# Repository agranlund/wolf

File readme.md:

## Wolfenstein 3D for Gameboy Color
 (c)2017 Anders Granlund, www.happydaze.se

A custom Gameboy Color cartridge: ATF1502 CPLD mapper, Kinetis KE04 (Cortex-M0+) as coprocessor working in tandem with Z80 on Gameboy. Commandlist and framebuffer sharing through dualport ram.

### Youtube: https://www.youtube.com/watch?v=3j6W-UF_7X0

## A rough description of what is included:

## /z80/
- ASM sourcecode for the Gameboy side, compile with WLA-DX (http://www.villehelin.com/wla.htm)
- Burn using a Gameboy flash cart programmer that support programming an AM29F040 chip via the AudioIn pin.
- I use the open-source C3 programmer from Jeff Frohwein
(https://reinerziegler.de.mirrors.gg8.se/readplus.htm#C3)
I'm sure there are more modern options out there but this is what have had since back when those things were the latest and greatest :)
Alternatively, burn the chip with a generic eprom programmer before soldering to board

## /z80/tools/
- mod2gbt, part of GBP Player 3.0.5. Built for Mac OSX.
- wla-gb, part of WLA-DX. Built for Mac OSX
- wlalink, part of WLA-DX. Built for Mac OSX

## /ke04/
- C sourcecode for MKE04Z128VLD4
- Build data using wolfgfx (makefile inside /ke04/test2/Data)
- Compile source+data with Kinetis Design Studio
- Burn with Segger J-link cable connected to SWI pins on cartridge

## /tools/wolfgfx/
- C++ source code for the map & graphics converter, with XCode project.

## /hardware/mbc/
- MBC1 clone for ATF1502AS(L)
- Compile with Atmel WinCUPL
- Burn with Atmel ATDH1150SUB cable connected to JTAG pins on cartridge

## /hardware/cart/
- Eagle & Gerber files for cartridge boards
- Rev.C use Nintendo MBC1 chip
- Rev.D use ATF1502 to clone MBC1 functionality
- Both are otherwise functionally identical
- Manufacture the board in 0.8mm height

## /hardware/link/
- Eagle & Gerber files for cartridge <-> JTAG & SWI cables
- Optional adapter to make connecting programming cables more convenient

## External libraries and credits

### Wolf4SDL:
Portions of this software derivate from Wolf4SDL by Moritz "Ripper" Kroll
(http://www.chaos-software.de.vu)

Wolf4SDL is in turned based on Wolfenstein 3D by id Software.
(http://www.idsoftware.com)

### FX HAMMER:
This software is using FX Hammer by Aleksi Eeben for generating and playing
sound effects. https://aleksieeben.myportfolio.com/portfolio

### GBT PLAYER:
This software is using GBT PLAYER v3.0.5 for music playback and for converting the
midis to runtime format. https://github.com/AntonioND/gbt-player

The converter tool in z80/tools/mod2gbt was built for MacOSX. Please see
the official GBT-Player Github page if you need to build it for another
operating system.

## License

 This hardware and software is free; you can redistribute it and/or
 modify it under the terms of the GNU General Public License
 as published by the Free Software Foundation; either version 2
 of the License, or (at your option) any later version.

 It is being distributed in the hope that it will be useful,
 but WITHOUT ANY WARRANTY; without even the implied warranty of
 MERCHANTABILITY or FITNESS FOR A PARTICULAR PURPOSE.  See the
 GNU General Public License for more details.

 The Z80 binary is using FX-Hammer and GBP Player. The authors of
 these must be credited and any of their respective copyright 
 notices and/or disclaimers must be included.

 The KE04 binary uses and/or takes inspiration from parts of
 Wolf4SDL source code by Moritz "Ripper" Kroll (http://www.chaos-software.de.vu)
 which was in turn based on Wolfenstein 3D sources released by id Software.

 Some data files are derivate from the Wolfenstein 3D shareware package.

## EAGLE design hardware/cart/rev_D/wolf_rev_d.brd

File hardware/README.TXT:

------------------------------------------------------------------------------
Wolf cartridge for Gameboy Color
(c)2017 Anders Granlund, www.happydaze.se

 This hardware is free; you can redistribute it and/or
 modify it under the terms of the GNU General Public License
 as published by the Free Software Foundation; either version 2
 of the License, or (at your option) any later version.

 It is being distributed in the hope that it will be useful,
 but WITHOUT ANY WARRANTY; without even the implied warranty of
 MERCHANTABILITY or FITNESS FOR A PARTICULAR PURPOSE.  See the
 GNU General Public License for more details.
------------------------------------------------------------------------------

Feel free to use this hardware as you see fit and in accordance to the
license agreement as long as I am being credited.

Notes:
The CY7C144E appears to have been discontinued.
IDT makes a drop in replacement called 7005L15PFG but I have
not personally tested with one.

These dual-port SRAMs are rather expensive and a better solution
might be to cost reduce by using FIFOs or normal SRAM with
some added logic.

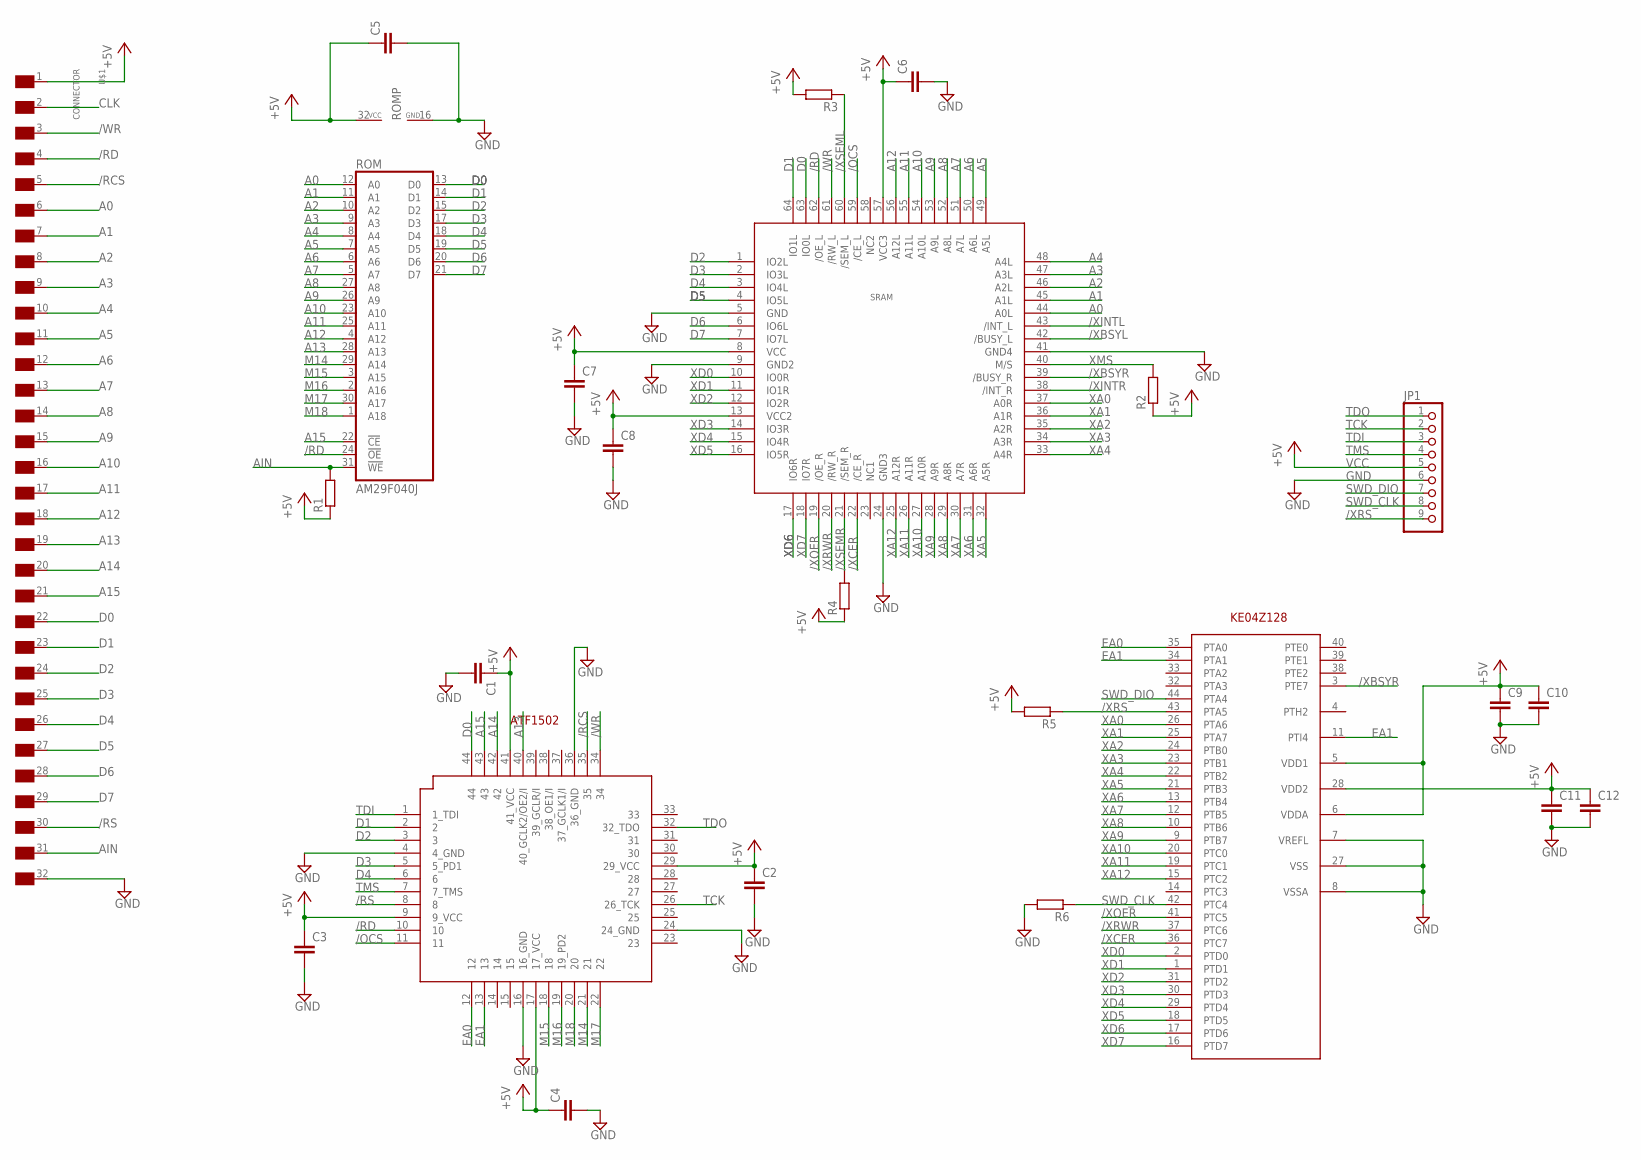
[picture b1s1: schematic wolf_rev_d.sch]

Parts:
ATF1502: ATF1502; TQFP44
C1, C2, C3, C4, C5, C6, C7, C8, C9, C10, C11, C12: C-EUC0805; C0805
JP1: PINHD-1X9; 1X09
KE04Z128: KE04Z128; TQFP44
R1, R2, R3, R4, R5, R6: R-EU_R0805; R0805
ROM: AM29F040J; PLCC32R
SRAM: CY7C144E; TQFP64
U$1: CONNECTOR

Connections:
+5V: ATF1502.9 (9_VCC), ATF1502.17 (17_VCC), ATF1502.29 (29_VCC), ATF1502.41 (41_VCC), C1.1, C2.1, C3.1, C4.1, C5.1, C6.1, C7.1, C8.1, C9.1, C10.1, C11.1, C12.1, JP1.5, KE04Z128.5 (VDD1), KE04Z128.6 (VDDA), KE04Z128.28 (VDD2), R1.1, R2.1, R3.2, R4.1, R5.2, ROM.32 (VCC), SRAM.8 (VCC), SRAM.13 (VCC2), SRAM.57 (VCC3), U$1.1 (VDD)
/OCS: ATF1502.11, SRAM.59 (/CE_L)
/RCS: ATF1502.35, U$1.5 (/RCS)
/RD: ATF1502.10, ROM.24 (!OE), SRAM.62 (/OE_L), U$1.4 (/RD)
/RS: ATF1502.8, U$1.30 (/RS)
/WR: ATF1502.34, SRAM.61 (/RW_L), U$1.3 (/WR)
/XBSYL: SRAM.42 (/BUSY_L)
/XBSYR: KE04Z128.3 (PTE7), SRAM.39 (/BUSY_R)
/XCER: KE04Z128.36 (PTC7), SRAM.22 (/CE_R)
/XINTL: SRAM.43 (/INT_L)
/XINTR: SRAM.38 (/INT_R)
/XOER: KE04Z128.41 (PTC5), SRAM.19 (/OE_R)
/XRS: JP1.9, KE04Z128.43 (PTA5), R5.1
/XRWR: KE04Z128.37 (PTC6), SRAM.20 (/RW_R)
/XSEML: R3.1, SRAM.60 (/SEM_L)
/XSEMR: R4.2, SRAM.21 (/SEM_R)
A0: ROM.12 (A0), SRAM.44 (A0L), U$1.6 (A0)
A1: ROM.11 (A1), SRAM.45 (A1L), U$1.7 (A1)
A2: ROM.10 (A2), SRAM.46 (A2L), U$1.8 (A2)
A3: ROM.9 (A3), SRAM.47 (A3L), U$1.9 (A3)
A4: ROM.8 (A4), SRAM.48 (A4L), U$1.10 (A4)
A5: ROM.7 (A5), SRAM.49 (A5L), U$1.11 (A5)
A6: ROM.6 (A6), SRAM.50 (A6L), U$1.12 (A6)
A7: ROM.5 (A7), SRAM.51 (A7L), U$1.13 (A7)
A8: ROM.27 (A8), SRAM.52 (A8L), U$1.14 (A8)
A9: ROM.26 (A9), SRAM.53 (A9L), U$1.15 (A9)
A10: ROM.23 (A10), SRAM.54 (A10L), U$1.16 (A10)
A11: ROM.25 (A11), SRAM.55 (A11L), U$1.17 (A11)
A12: ROM.4 (A12), SRAM.56 (A12L), U$1.18 (A12)
A13: ATF1502.40 (40_GCLK2/OE2/I), ROM.28 (A13), U$1.19 (A13)
A14: ATF1502.42, U$1.20 (A14)
A15: ATF1502.43, ROM.22 (!CE), U$1.21 (A15)
AIN: R1.2, ROM.31 (!WE), U$1.31 (VIN)
CLK: U$1.2 (NC)
D0: ATF1502.44, ROM.13 (D0), SRAM.63 (IO0L), U$1.22 (D0)
D1: ATF1502.2, ROM.14 (D1), SRAM.64 (IO1L), U$1.23 (D1)
D2: ATF1502.3, ROM.15 (D2), SRAM.1 (IO2L), U$1.24 (D2)
D3: ATF1502.5 (5_PD1), ROM.17 (D3), SRAM.2 (IO3L), U$1.25 (D3)
D4: ATF1502.6, ROM.18 (D4), SRAM.3 (IO4L), U$1.26 (D4)
D5: ROM.19 (D5), SRAM.4 (IO5L), U$1.27 (D5)
D6: ROM.20 (D6), SRAM.6 (IO6L), U$1.28 (D6)
D7: ROM.21 (D7), SRAM.7 (IO7L), U$1.29 (D7)
EA0: ATF1502.12, KE04Z128.35 (PTA0)
EA1: ATF1502.13, KE04Z128.11 (PTI4), KE04Z128.34 (PTA1)
GND: ATF1502.4 (4_GND), ATF1502.16 (16_GND), ATF1502.24 (24_GND), ATF1502.36 (36_GND), C1.2, C2.2, C3.2, C4.2, C5.2, C6.2, C7.2, C8.2, C9.2, C10.2, C11.2, C12.2, JP1.6, KE04Z128.7 (VREFL), KE04Z128.8 (VSSA), KE04Z128.27 (VSS), R6.2, ROM.16 (GND), SRAM.5 (GND), SRAM.9 (GND2), SRAM.24 (GND3), SRAM.41 (GND4), U$1.32 (GND)
M14: ATF1502.21, ROM.29 (A14)
M15: ATF1502.18, ROM.3 (A15)
M16: ATF1502.19 (19_PD2), ROM.2 (A16)
M17: ATF1502.22, ROM.30 (A17)
M18: ATF1502.20, ROM.1 (A18)
SWD_CLK: JP1.8, KE04Z128.42 (PTC4), R6.1
SWD_DIO: JP1.7, KE04Z128.44 (PTA4)
TCK: ATF1502.26 (26_TCK), JP1.2
TDI: ATF1502.1 (1_TDI), JP1.3
TDO: ATF1502.32 (32_TDO), JP1.1
TMS: ATF1502.7 (7_TMS), JP1.4
XA0: KE04Z128.26 (PTA6), SRAM.37 (A0R)
XA1: KE04Z128.25 (PTA7), SRAM.36 (A1R)
XA2: KE04Z128.24 (PTB0), SRAM.35 (A2R)
XA3: KE04Z128.23 (PTB1), SRAM.34 (A3R)
XA4: KE04Z128.22 (PTB2), SRAM.33 (A4R)
XA5: KE04Z128.21 (PTB3), SRAM.32 (A5R)
XA6: KE04Z128.13 (PTB4), SRAM.31 (A6R)
XA7: KE04Z128.12 (PTB5), SRAM.30 (A7R)
XA8: KE04Z128.10 (PTB6), SRAM.29 (A8R)
XA9: KE04Z128.9 (PTB7), SRAM.28 (A9R)
XA10: KE04Z128.20 (PTC0), SRAM.27 (A10R)
XA11: KE04Z128.19 (PTC1), SRAM.26 (A11R)
XA12: KE04Z128.15 (PTC2), SRAM.25 (A12R)
XD0: KE04Z128.2 (PTD0), SRAM.10 (IO0R)
XD1: KE04Z128.1 (PTD1), SRAM.11 (IO1R)
XD2: KE04Z128.31 (PTD2), SRAM.12 (IO2R)
XD3: KE04Z128.30 (PTD3), SRAM.14 (IO3R)
XD4: KE04Z128.29 (PTD4), SRAM.15 (IO4R)
XD5: KE04Z128.18 (PTD5), SRAM.16 (IO5R)
XD6: KE04Z128.17 (PTD6), SRAM.17 (IO6R)
XD7: KE04Z128.16 (PTD7), SRAM.18 (IO7R)
XMS: R2.2, SRAM.40 (M/S)

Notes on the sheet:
VCC
GND

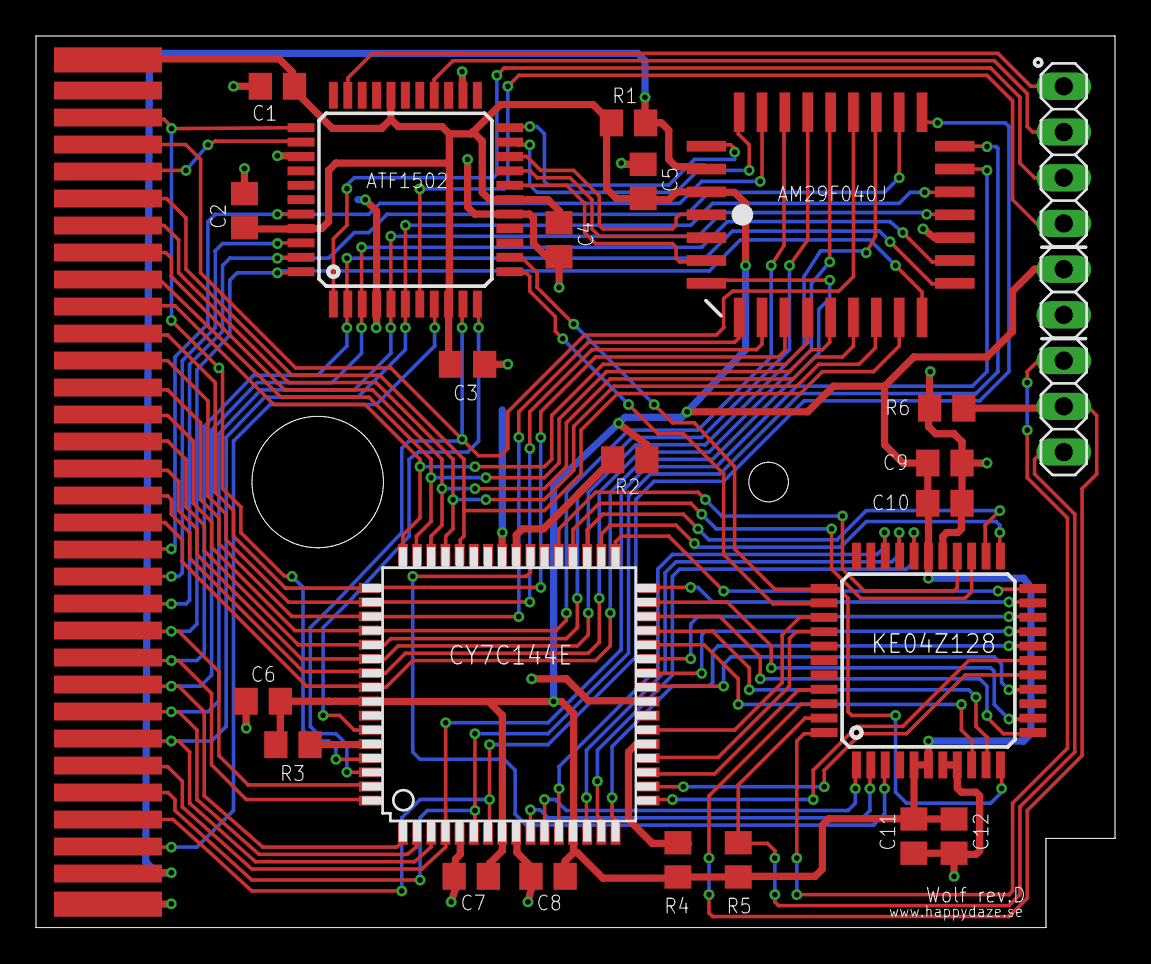
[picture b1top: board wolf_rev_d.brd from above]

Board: 2 copper layers, 59.9 x 49.5 mm, 24 parts (0 on the bottom side), 74 nets.

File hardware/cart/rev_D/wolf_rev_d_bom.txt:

Part		Device/Value		Package
------------------------------------------------
ATF1502		ATF1502AS-7AX44		TQFP44
KE04Z128	KE04Z128VLD4		TQFP44
CY7C144E	CY7C144E-55AXC		TQFP64
AM29F040J	AM29F040J		PLCC32R
C1		0.1uF			0805
C2		0.1uF			0805
C3		0.1uF			0805
C4		0.1uF			0805
C5		0.1uF			0805
C6		0.1uF			0805
C7		0.1uF			0805
C8		0.1uF			0805
C9		1.0uF			0805
C10		0.1uF			0805
C11		0.1uF			0805
C12		1.0uF			0805
R1		47k			0805
R2		47k			0805
R3		47k			0805
R4		47k			0805
R5		47k			0805
R6		47k			0805

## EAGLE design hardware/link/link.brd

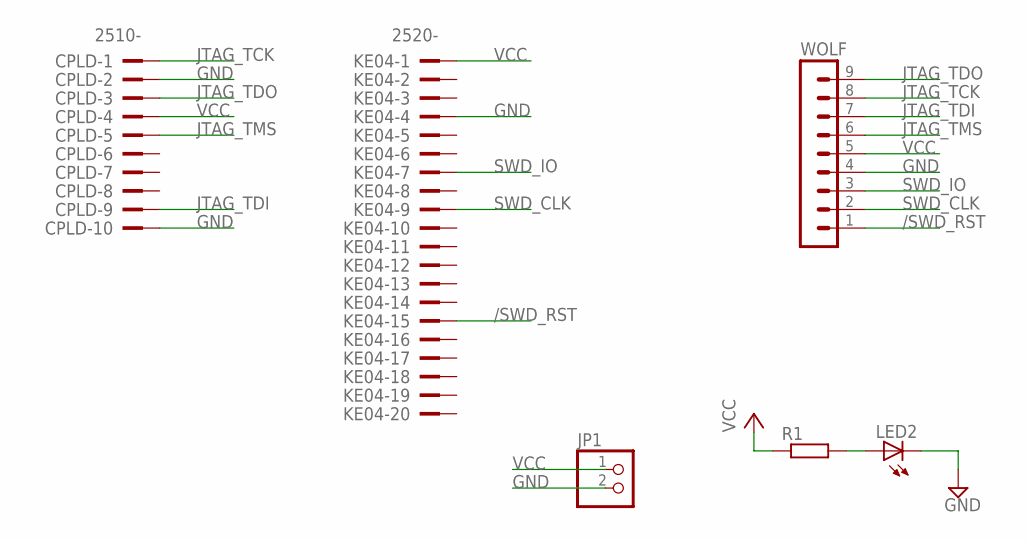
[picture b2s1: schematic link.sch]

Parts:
CPLD: 2510-; PAK100/2500-10
JP1: PINHD-1X2; 1X02
KE04: 2520-; PAK100/2500-20
LED2: LEDSML0805; SML0805
R1: R-EU_R0805; R0805
WOLF: MA09-1

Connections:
/SWD_RST: KE04.15, WOLF.1
GND: CPLD.2, CPLD.10, JP1.2, KE04.4, LED2.C, WOLF.4
JTAG_TCK: CPLD.1, WOLF.8
JTAG_TDI: CPLD.9, WOLF.7
JTAG_TDO: CPLD.3, WOLF.9
JTAG_TMS: CPLD.5, WOLF.6
unnamed: LED2.A, R1.2
SWD_CLK: KE04.9, WOLF.2
SWD_IO: KE04.7, WOLF.3
VCC: CPLD.4, JP1.1, KE04.1, R1.1, WOLF.5

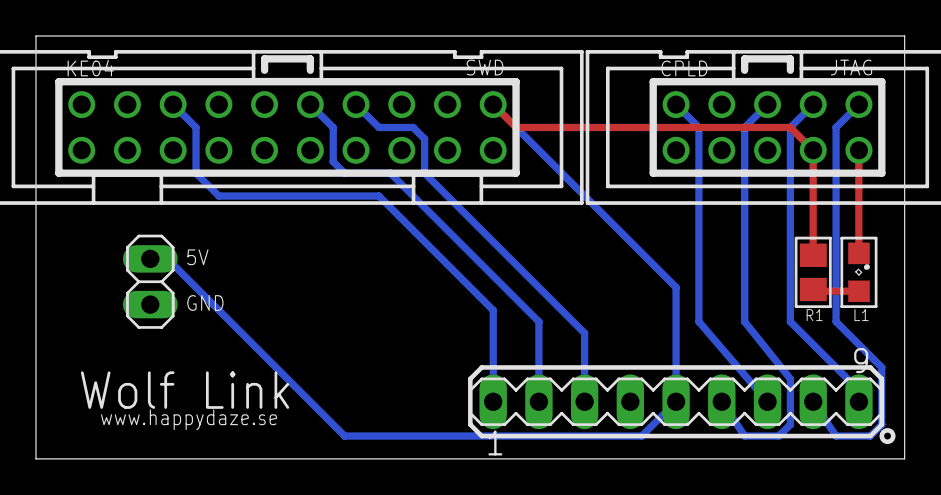
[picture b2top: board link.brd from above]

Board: 2 copper layers, 48.3 x 23.5 mm, 6 parts (0 on the bottom side), 10 nets.
